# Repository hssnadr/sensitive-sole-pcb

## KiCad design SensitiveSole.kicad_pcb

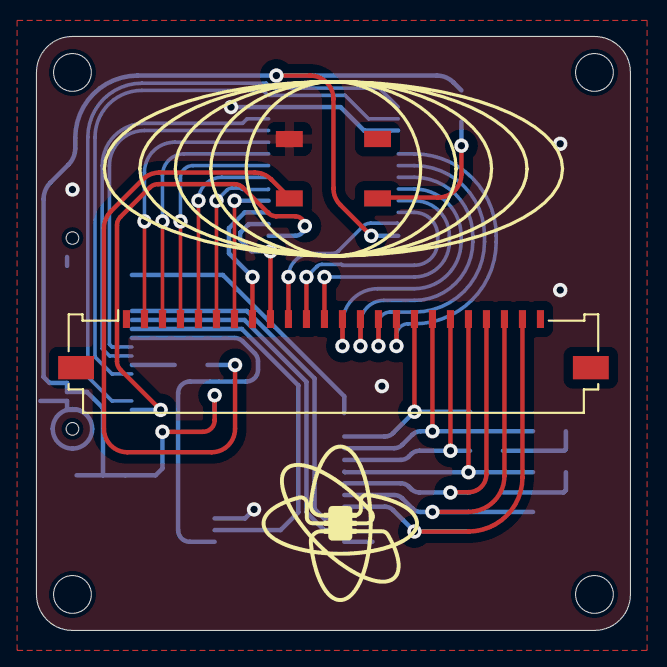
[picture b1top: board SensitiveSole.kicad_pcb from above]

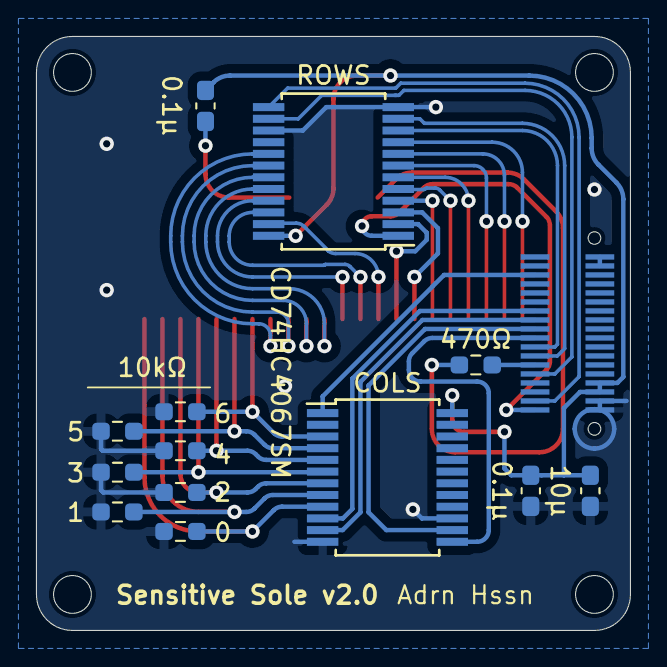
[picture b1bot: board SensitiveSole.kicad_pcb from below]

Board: 2 copper layers, 33.0 x 33.0 mm, 17 parts (14 on the bottom side), 38 nets.

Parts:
0: 10kΩ; R_0603_1608Metric_Pad0.98x0.95mm_HandSolder
0#2: 0.1µ; C_0603_1608Metric_Pad1.08x0.95mm_HandSolder
1, 2, 3, 4, 5, 6: 10k; R_0603_1608Metric_Pad0.98x0.95mm_HandSolder
BOTTOM_DF12: DF12-36NOLEGS-MALE; DF12-36-DP-NL
C1: 0.1µ; C_0603_1608Metric_Pad1.08x0.95mm_HandSolder
C2: 10µ; C_0603_1608Metric_Pad1.08x0.95mm_HandSolder
COLS: CD74HC4067SM; SSOP-24_5.3x8.2mm_P0.65mm
D1: WS2812B; LED_WS2812B_PLCC4_5.0x5.0mm_P3.2mm
FPC1: Conn_01x24; Molex_200528-0240_1x24-1MP_P1.00mm_Horizontal
R8: 470Ω; R_0603_1608Metric_Pad0.98x0.95mm_HandSolder
ROWS: CD74HC4067SM; SSOP-24_5.3x8.2mm_P0.65mm
U$8: LOGO_MOVUINOBOTTOM_11MM; LOGO-NoName_MOVUINO_BMP_11MM-TOP

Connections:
+3.3V: 0#2.1, BOTTOM_DF12.30, BOTTOM_DF12.32, C1.1, C2.1, COLS.24 (VCC), ROWS.24 (VCC)
+5V: BOTTOM_DF12.2, BOTTOM_DF12.4
/COL0: 0.2, COLS.9 (I0), FPC1.23
/COL1: 1.2, COLS.8 (I1), FPC1.22
/COL2: 2.2, COLS.7 (I2), FPC1.21
/COL3: 3.2, COLS.6 (I3), FPC1.20
/COL4: 4.2, COLS.5 (I4), FPC1.19
/COL5: 5.2, COLS.4 (I5), FPC1.18
/COL6: 6.2, COLS.3 (I6), FPC1.17
/IO2: BOTTOM_DF12.35, ROWS.1 (COM)
/IO5: BOTTOM_DF12.33, ROWS.13 (S3)
/IO12: BOTTOM_DF12.27, ROWS.14 (S2)
/IO14: BOTTOM_DF12.23, ROWS.11 (S1)
/IO15: BOTTOM_DF12.25, R8.1
/IO25: BOTTOM_DF12.17, COLS.14 (S2)
/IO26: BOTTOM_DF12.19, COLS.13 (S3)
/IO27: BOTTOM_DF12.21, ROWS.10 (S0)
/IO32: BOTTOM_DF12.13, COLS.10 (S0)
/IO33: BOTTOM_DF12.15, COLS.11 (S1)
/IO39: BOTTOM_DF12.5, COLS.1 (COM)
/ROW0: FPC1.2, ROWS.9 (I0)
/ROW1: FPC1.3, ROWS.8 (I1)
/ROW2: FPC1.4, ROWS.7 (I2)
/ROW3: FPC1.5, ROWS.6 (I3)
/ROW4: FPC1.6, ROWS.5 (I4)
/ROW5: FPC1.7, ROWS.4 (I5)
/ROW6: FPC1.8, ROWS.3 (I6)
/ROW7: FPC1.9, ROWS.2 (I7)
/ROW8: FPC1.10, ROWS.23 (I8)
/ROW9: FPC1.11, ROWS.22 (I9)
/ROW10: FPC1.12, ROWS.21 (I10)
/ROW11: FPC1.13, ROWS.20 (I11)
/ROW12: FPC1.14, ROWS.19 (I12)
/ROW13: FPC1.15, ROWS.18 (I13)
/ROW14: FPC1.16, ROWS.17 (I14)
GND: 0.1, 1.1, 2.1, 3.1, 4.1, 5.1, 6.1, BOTTOM_DF12.34, BOTTOM_DF12.36, C1.2, C2.2, COLS.12 (GND), COLS.15 (~E), D1.1 (VSS), ROWS.12 (GND), ROWS.15 (~E)
unnamed: D1.2 (DIN), R8.2
unnamed: 0#2.2, D1.3 (VDD)

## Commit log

2023-11-13 base clean
2023-11-15 v0.99
2023-11-15 graphism
2023-11-21 remove warnings
2023-12-11 ready to order
